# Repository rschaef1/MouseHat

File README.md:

# MouseHat
A remote-control deep brain stimulation device with customizable frequency, amplitude, and pulse-width.

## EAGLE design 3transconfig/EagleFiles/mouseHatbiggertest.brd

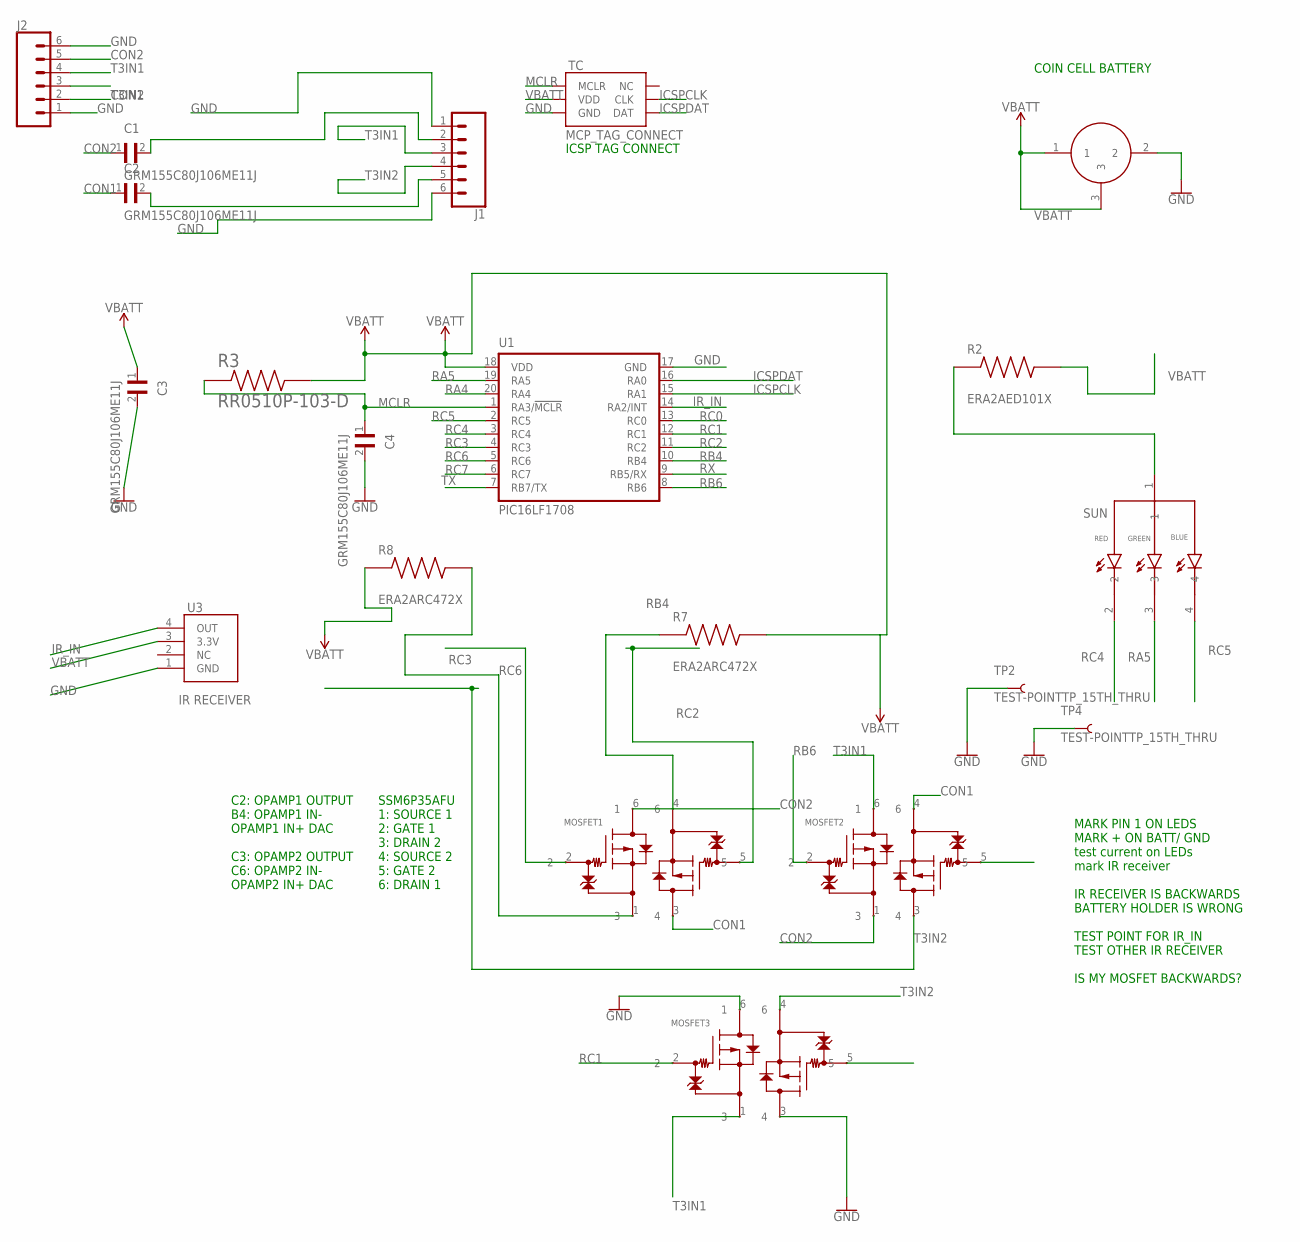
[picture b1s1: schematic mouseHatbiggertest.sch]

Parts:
C1, C2, C3, C4: GRM155C80J106ME11J; CAPC1005X70N
J1, J2: CONN_06NO_SILK_FEMALE_PTH; 1X06_NO_SILK
MOSFET1, MOSFET2, MOSFET3: SSM6P35AFE,LF; ES6_TOS
R2: ERA2AED101X; RES_ERA2AED101X
R3: RR0510P-103-D; RESC1005X40N
R7, R8: ERA2ARC472X; RES_ERA2ARC472X
TC: MCP_TAG_CONNECT; TAG_CONNECT_MCP
TP2, TP4: TEST-POINTTP_15TH_THRU; TP_15TH
U1: PIC16LF1708; QFN20
U3: IR RECEIVER; TSOP6238
U$2: 10MM_BATT_HOLDER
U$6: SUN; LED_RGB_SUN

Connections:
CON1: C2.1, J2.2, MOSFET1.3 (4), MOSFET2.4 (6)
CON2: C1.1, J2.5, MOSFET1.6 (1), MOSFET2.1 (3)
GND: C3.2, C4.2, J1.1, J1.6, J2.1, J2.6, MOSFET3.3 (4), MOSFET3.6 (1), TC.3 (GND), TP2.P$1, TP4.P$1, U1.17 (GND), U3.1 (GND), U$2.2
ICSPCLK: TC.5 (CLK), U1.15 (RA1)
ICSPDAT: TC.4 (DAT), U1.16 (RA0)
IR_IN: U1.14 (RA2/INT), U3.4 (OUT)
MCLR: C4.1, R3.1, TC.1 (MCLR), U1.1 (RA3/!MCLR)
unnamed: C2.2, J1.5
unnamed: R2.1, U$6.1
unnamed: C1.2, J1.2
RA4: U1.20 (RA4)
RA5: U1.19 (RA5), U$6.3
RB4: MOSFET1.4 (6), R7.1, U1.10 (RB4)
RB6: MOSFET2.2, U1.8 (RB6)
RC0: MOSFET2.5, U1.13 (RC0)
RC1: MOSFET3.2, U1.12 (RC1)
RC2: MOSFET1.5, U1.11 (RC2)
RC3: MOSFET1.2, U1.4 (RC3)
RC4: U1.3 (RC4), U$6.2
RC5: U1.2 (RC5), U$6.4
RC6: MOSFET1.1 (3), R8.2, U1.5 (RC6)
RC7: MOSFET3.5, U1.6 (RC7)
RX: U1.9 (RB5/RX)
T3IN1: J1.3, J2.4, MOSFET2.6 (1), MOSFET3.1 (3)
T3IN2: J1.4, J2.3, MOSFET2.3 (4), MOSFET3.4 (6)
TX: U1.7 (RB7/TX)
VBATT: C3.1, R2.2, R3.2, R7.2, R8.1, TC.2 (VDD), U1.18 (VDD), U3.3 (3.3V), U$2.1, U$2.3

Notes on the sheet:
COIN CELL BATTERY
C2: OPAMP1 OUTPUT B4: OPAMP1 IN- OPAMP1 IN+ DAC C3: OPAMP2 OUTPUT C6: OPAMP2 IN- OPAMP2 IN+ DAC
SSM6P35AFU 1: SOURCE 1 2: GATE 1 3: DRAIN 2 4: SOURCE 2 5: GATE 2 6: DRAIN 1
MARK PIN 1 ON LEDS MARK + ON BATT/ GND test current on LEDs mark IR receiver IR RECEIVER IS BACKWARDS BATTERY HOLDER IS WRONG TEST POINT FOR IR_IN TEST OTHER IR RECEIVER IS MY MOSFET BACKWARDS?
ICSP TAG CONNECT

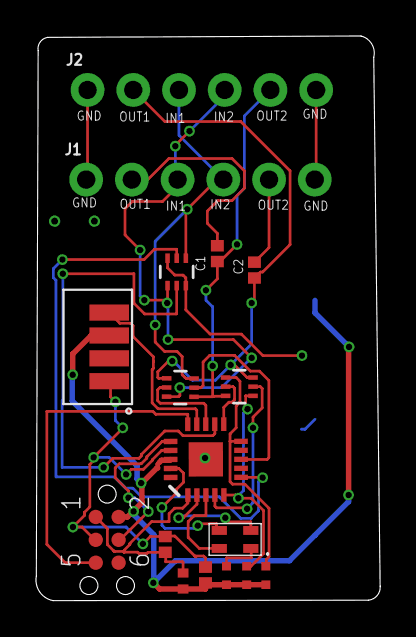
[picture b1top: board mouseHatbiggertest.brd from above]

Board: 2 copper layers, 19.1 x 31.4 mm, 20 parts (1 on the bottom side), 24 nets.

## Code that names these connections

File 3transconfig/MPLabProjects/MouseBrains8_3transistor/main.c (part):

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}

// initialize the registers for LED PWM generation
// note: blue using CCP1 output on pin RC5
//       red using PWM3 output on pin RC4
//       green using PWM4 output on pin RA5
void initLED()
{
  // init timer2, used as base for all three PWM outputs
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  // note: CCP1 does not have selectable PWM polarity
  //       so period value must be flipped
  TRISC |= 0b00100000; // disable RC5 output
  RC5PPS = 0b01100; // route CCP1 output to RC5 pin
  CCP1CONbits.CCP1M = 0b1100; // CCP1 in PWM mode
  CCPR1L = 255; // initial duty cycle = 1023, which is off for common anode
  CCP1CONbits.DC1B = 0x3; // initial duty cycle = 1023, off for C.A.
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}

void LATCH_Initialize() {
 /*   TRISBbits.TRISB6 = 0; // set RB6 and RA0 as outputs
    TRISCbits.TRISC0 = 0; // TRIS sets direction: 0 is output
    TRISCbits.TRISC1 = 0;
    TRISCbits.TRISC7 = 0; 
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
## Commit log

2022-05-03 Create testing

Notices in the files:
3transconfig/MPLabProjects/MouseBrains8_3transistor/main.c:
(c) 2018 Microchip Technology Inc. and its subsidiaries.
parts and their libraries:
SparkFun-Connectors: Licensing: Creative Commons ShareAlike 4.0 International - https://creativecommons.org/licenses/by-sa/4.0
COPYRIGHT: Copyright (C) 2021 Ultra Librarian. All rights reserved.
